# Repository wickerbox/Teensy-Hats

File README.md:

# Teensy-Hats
Collection of daughter boards for Paul Stoffregen's Teensy

- LiDAR Teensy Hat
- Temperature Monitor Hat

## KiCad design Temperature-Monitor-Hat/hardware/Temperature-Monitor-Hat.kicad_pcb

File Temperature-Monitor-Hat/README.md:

# Temperature Monitor LCD Teensy Hat

Simple monitor hat with an LCD screen that displays current temperature as sensed by K-type thermocouple through the MAX31855 junction-compensated sensor chip. The board also buzzes at certain preset temperatures. 

|Ref|Qty|Description|Manufacturer|Mfr PN|Vendor|Vendor PN|
|---|---|-----------|------------|------|------|---------|
|J1|1|TEENSY 3.2 32BIT 72MHZ|PJRC|TEENSY3.2|PJRC|TEENSY3.2|
|U1|1|IC CONV THERMOCOUPLE MAX31855 SOIC8|Freescale NXP|MAX31855KASA+|Digikey|MAX31855KASA+-ND|
|LCD1|1|LCD MODULE 16X2 CHARACTER 1602A|Tinsharp|TC1602A-09T|Adafruit|181|
|C1;C2|2|CAP CER 0.1UF 100V X7R 0603|Murata|GRM188R72A104KA35D|Digikey|490-3285-1-ND|
|J2|1|CONN TERM SCREW GREEN 2.54MM 2POS TH|OnShoreTech|OSTVN02A150|Digikey|ED10561-ND|
|R1|1|TRIMMER 10K OHM TH|Bourns|3362U-1-103LF|Digikey|3362U-103LF-ND|
|SPK1|1|BUZZER ONE NOTE 3V 4KHZ PIEZO SMT|CUI Inc|CMT-1603-SMT-TR|Digikey|102-1193-1-ND|

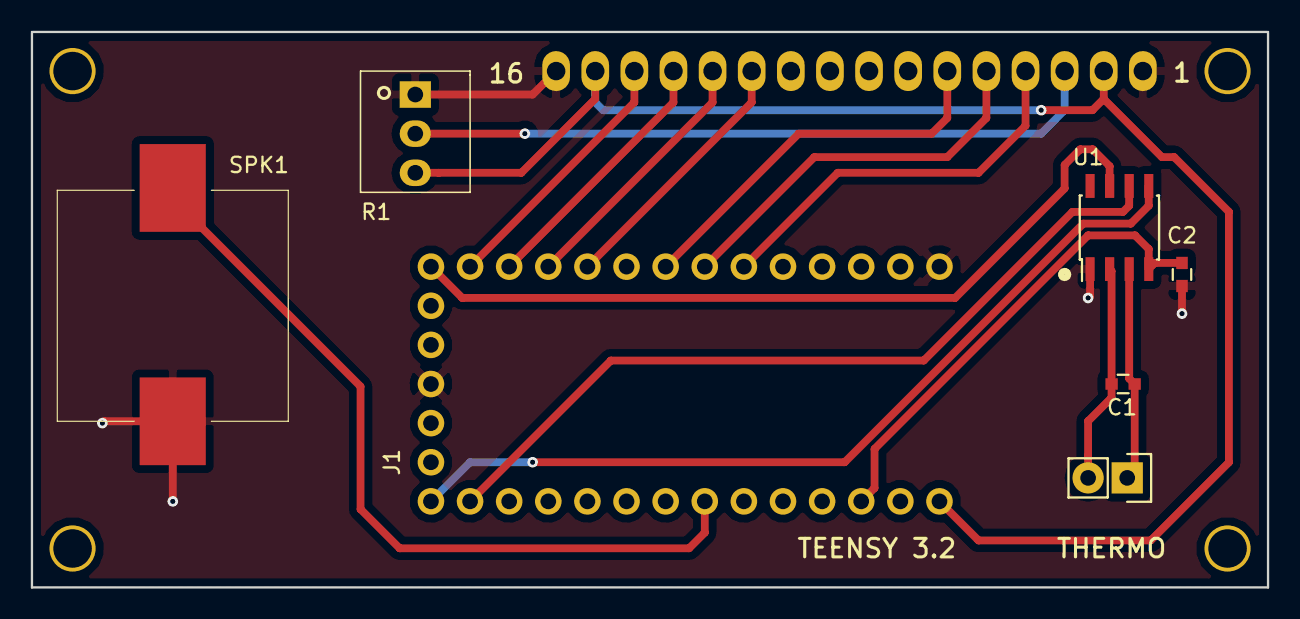
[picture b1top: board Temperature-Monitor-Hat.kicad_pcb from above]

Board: 2 copper layers, 80.3 x 36.1 mm, 8 parts (1 on the bottom side), 17 nets.

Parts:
C1, C2: 100nF; RLC-0603-SMD
J1: TEENSY3.2-72MHz; TEENSY-3.2-NOSILK
J2: THERMO; CONN-ONSHORE-SCREW-GREEN-2PIN-TH
LCD1: LCD-MODULE-16X2-CHARACTER-1602A-CUSTOM1; LCD-1602A
R1: 10K; RES-TRIMPOT-BOURNS-3362-SQUARE-TH-CENTER
SPK1: BUZZER; SPEAKER-CMT-1603
U1: MAX31855; SOIC-8-3.9x4.9MM-P1.27MM

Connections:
+3V3: C2.1, J1.3V1, J1.3V2, U1.4
+5V: J1.VIN, LCD1.2, LCD1.15, R1.3
GND: C2.2, J1.G1, J1.G2, LCD1.1, LCD1.16, R1.1, SPK1.2, U1.1
unnamed: C1.1, J2.1, U1.3
unnamed: C1.2, J2.2, U1.2
unnamed: J1.4, LCD1.4
unnamed: J1.5, LCD1.5
unnamed: J1.6, LCD1.6
unnamed: J1.8, LCD1.11
unnamed: J1.9, LCD1.12
unnamed: J1.10, LCD1.13
unnamed: J1.11, LCD1.14
unnamed: J1.12, U1.7
unnamed: J1.13, U1.5
unnamed: J1.14, U1.6
unnamed: J1.20, SPK1.1
unnamed: LCD1.3, R1.2

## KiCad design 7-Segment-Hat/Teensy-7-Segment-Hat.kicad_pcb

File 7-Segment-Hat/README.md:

# 7-Segment Display Teensy Hat

7-Segment display daughter board for the Teensy 3.2 with onboard microSD card.

I'll share the boards at OSH Park when the design is verified. You can buy a set of three for $5.20.

|Ref|Qty|Description|MF_Name|MF_PN|Digikey|
|---|---|-----------|-------|-----|-------|
|J3|1|CONN MICRO SD CARD HINGED TYPE|Molex|5009010801|WM19081CT-ND|
|LED1|1|LED DISPLAY 4CHAR 7SEGMENT COMMON CATHODE LTC-4727JR|LITE-ON|LTC-4727JR|160-1551-5-ND|
|R1-R4|4|RES SMD 470 OHM 5% 1/4W 0603|Rohm Semi|ESR03EZPJ471|RHM470DCT-ND|

The best way to place the LCD 7-Segment Display and the Teensy 3.2 is to buy one 40-position header (it's the cheapest option, about $0.50) and snap it apart into the sections you need.

The Teensy 3.2 can be bought from OSH Park at checkout, or from <a href="http://pjrc.com/store/teensy32.html">PJRC</a>.

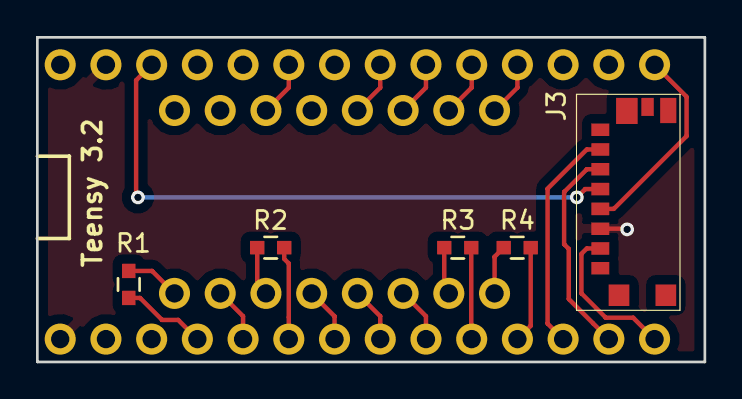
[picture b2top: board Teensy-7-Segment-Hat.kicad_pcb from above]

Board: 2 copper layers, 37.1 x 18.0 mm, 7 parts (1 on the bottom side), 23 nets.

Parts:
J1: TEENSY3.2-72MHz-SIMPLE; TEENSY-3.2-SIMPLE
J3: MICRO-SD; CONN-SD-MICRO-MOLEX-0475710001
LED1: LED-4x7-SEGMENT-LTC-4727JR; DIP-16-W10.16MM-CIRCLEPADS
R1, R2, R3, R4: 470; RLC-0603-SMD

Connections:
+3V3: J1.3V2, J3.4
/A: J1.18, LED1.14
/B: J1.16, LED1.16
/C: J1.19, LED1.13
/D: J1.7, LED1.3
/DIGIT1: J1.9, R4.1
/DIGIT2: J1.8, R3.1
/DIGIT3: J1.4, R2.1
/DIGIT4: J1.2, R1.1
/DP: J1.3, LED1.7
/E: J1.5, LED1.5
/F: J1.21, LED1.11
/G: J1.17, LED1.15
/L: J1.6, LED1.4
/MISO: J1.12, J3.7
/MOSI: J1.11, J3.3
/SCLK: J1.13, J3.5
/SD_CS: J1.10, J3.2
GND: J1.AG, J1.G1, J3.6
unnamed: LED1.1, R4.2
unnamed: LED1.2, R3.2
unnamed: LED1.6, R2.2
unnamed: LED1.8, R1.2

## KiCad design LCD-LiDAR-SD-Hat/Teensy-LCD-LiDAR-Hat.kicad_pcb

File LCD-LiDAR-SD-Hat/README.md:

# LCD-LiDAR-SD Teensy Hat

LiDAR board with LCD screen and SD card for logging. 

The project is released as open hardware under the CERN v1.2 Open Hardware license.

It uses a LiDAR-Lite v1 or v2 for the rangefinder, and it supports the I2C and PWM modes. The project uses the KiCad Teensy template and footprint from <a href="http://wickerbox.net/wickerlib">wickerlib</a>. 

I've shared the project at OSH Park so you can buy a set of three bare boards for $22.55.

The Teensy 3.2 is available at <a href="http://pjrc.com/teensy/index.html">PJRC.com</a> or at OSH Park as an add-on at checkout.

I'm using a standard <a href="https://www.adafruit.com/product/181">16x2 LCD screen from Adafruit</a>, but you can also get them from Amazon.

The rest of the parts are available at <a href="http://digikey.com">Digikey</a>.

|Ref|Qty|Description|Manuf|Mfr PN|Source PN|
|---|---|-----------|-----|------|---------|
|J2|1|HEADER FEMALE 6POS TH 1x06 0.1”|Harwin|M20-7820642|952-1808-ND|
|J3|1|CONN MICRO SD CARD |Molex|0475710001|WM9731CT-ND|
|LED1-2|2|LED AMBER DIFFUSED 0603 SMD|OSRAM Opto|LA L296-Q2R2-1-Z|475-2712-1-ND|
|R1-R5,R7|6|RES SMD 1K OHM 1% 1/10W 0603|Samsung|RC1608F102CS|1276-3484-1-ND|
|R6|1|TRIMMER 10K OHM TH |Bourns| 3362U-1-103LF|3362U-103LF-ND|
|S1-S3|3|SWITCH TACTILE SPST-NO 0.05A 12V|Omron|B3U-1000P|SW1020CT-ND|

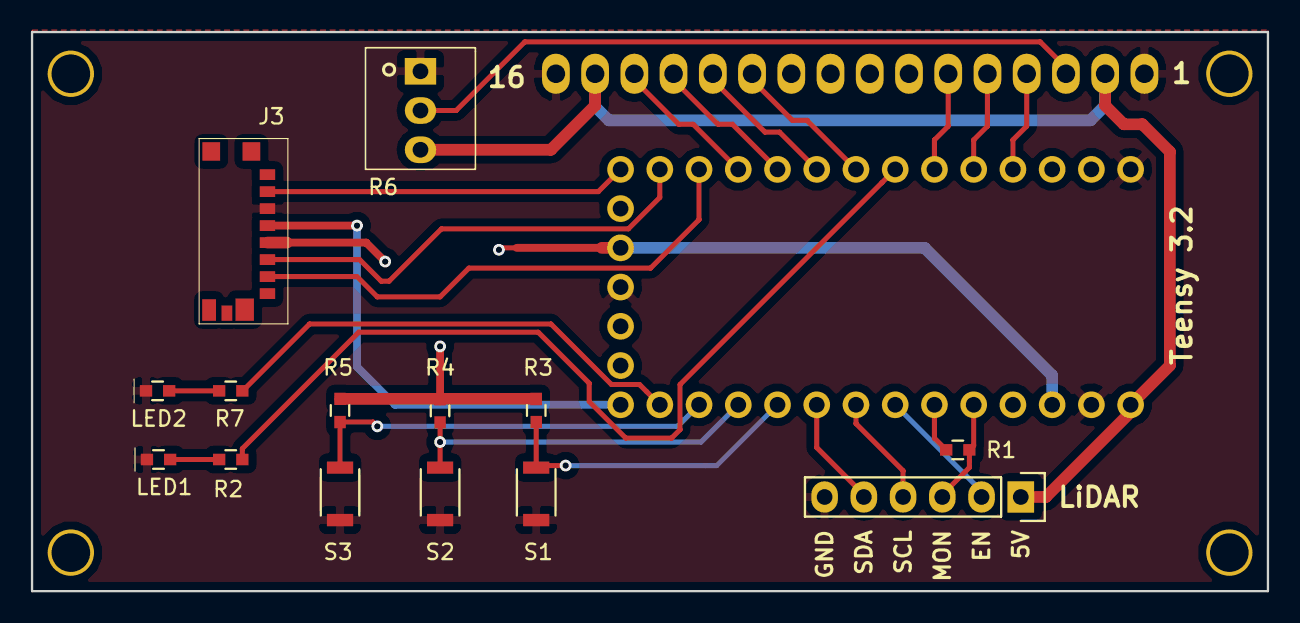
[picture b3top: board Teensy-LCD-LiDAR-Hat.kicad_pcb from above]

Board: 2 copper layers, 80.0 x 36.2 mm, 16 parts (1 on the bottom side), 27 nets.

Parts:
J1: TEENSY3.2-72MHz; TEENSY-3.2-NOSILK
J2: LIDAR-LITE; CONN-HEADER-STRAIGHT-P2.54MM-1x06
J3: MICRO-SD; CONN-SD-MICRO-MOLEX-0475710001
LCD1: LCD-16x2; LCD-1602A
LED1, LED2: AMBER; LED-0603-SMD
R1, R2, R3, R4, R5, R7: 1K; RLC-0603-SMD
R6: 10K; RES-TRIMPOT-BOURNS-3362-SQUARE-TH-CENTER
S1: BUTTON1; SWITCH-OMRON-MOMENTARY-SMD-B3U-1000P
S2: BUTTON2; SWITCH-OMRON-MOMENTARY-SMD-B3U-1000P
S3: BUTTON3; SWITCH-OMRON-MOMENTARY-SMD-B3U-1000P

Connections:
+3V3: J1.3V1, J1.3V2, J3.4, R3.1, R4.1, R5.1
+5V: J1.VIN, J2.1, LCD1.2, LCD1.15, R6.3
/BUTTON1: J1.17, R3.2, S1.1
/BUTTON2: J1.16, R4.2, S2.1
/BUTTON3: J1.15, R5.2, S3.1
/LCD_D4: J1.6, LCD1.11
/LCD_D5: J1.7, LCD1.12
/LCD_D6: J1.8, LCD1.13
/LCD_D7: J1.9, LCD1.14
/LCD_EN: J1.4, LCD1.6
/LCD_RS: J1.2, LCD1.4
/LCD_RW: J1.3, LCD1.5
/LED1: J1.5, R2.1
/LED2: J1.14, R7.1
/LIDAR_EN: J1.20, J2.2
/LIDAR_MONITOR: J1.22, J2.3, R1.2
/LIDAR_TRIGGER: J1.21, R1.1
/MISO: J1.12, J3.7
/MOSI: J1.11, J3.3
/SCL: J1.19, J2.4
/SCLK: J1.13, J3.5
/SDA: J1.18, J2.5
/SD_CS: J1.10, J3.2
GND: J1.AG, J1.G1, J1.G2, J2.6, J3.6, LCD1.1, LCD1.16, LED1.1, LED2.1, R6.1, S1.2, S2.2, S3.2
unnamed: LCD1.3, R6.2
unnamed: LED1.2, R2.2
unnamed: LED2.2, R7.2

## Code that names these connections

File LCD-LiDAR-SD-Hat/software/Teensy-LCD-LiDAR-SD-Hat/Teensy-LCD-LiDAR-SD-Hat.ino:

/***************************************************

  Jenner Hanni / Wickerbox Electronics Notes
  See the Github repo: https://github.com/wickerbox/Teensy-Hats/

****************************************************/


#include <SPI.h>
#include "SdFat.h"
#include <LiquidCrystal.h>

// Hook up to the SD card over SPI
// Assumes 11 MOSI, 12 MISO, 13 SCLK
int SDCS_Pin = 10;
SdFat SD;

// LCD
// LiquidCrystal lcd(rs, rw, enable, d4, d5, d6, d7)
LiquidCrystal lcd(2, 3, 4, 6, 7, 8, 9);

// LEDs and Buttons
int LED1_Pin = 5;
int LED2_Pin = 14;
int Button1_Pin = 17;
int Button2_Pin = 16;
int Button3_Pin = 15;

// LiDAR Setup
int LiDAR_Trigger_Pin = 21;
int LiDAR_Monitor_Pin = 22;
int LiDAR_Enable_Pin = 20;
int LiDAR_SDA_Pin = 18;
int LiDAR_SCL_Pin = 19;
unsigned long pulse_width;

void readLiDAR() {
  pulse_width = pulseIn(LiDAR_Monitor_Pin, HIGH); // Count how long the pulse is high in microseconds
  if (pulse_width != 0) { // If we get a reading that isn't zero, let's print it
    pulse_width = pulse_width / 10; // 10usec = 1 cm of distance for LIDAR-Lite
  }
}

void setup() {

  Serial.begin(9600);
  delay(1000);
  Serial.println("The program is on.");
  delay(1000);

  // Setup the LiDAR Rangefinder
  pinMode(LiDAR_Trigger_Pin, OUTPUT);
  pinMode(LiDAR_Monitor_Pin, INPUT);
  pinMode(LiDAR_Enable_Pin, OUTPUT);
  digitalWrite(LiDAR_Enable_Pin, HIGH); // turn sensor on
  digitalWrite(LiDAR_Trigger_Pin, LOW); // set for continuous read

  // Setup the buttons and LEDs
  pinMode(LED1_Pin, OUTPUT);
  pinMode(LED2_Pin, OUTPUT);
  pinMode(Button1_Pin, INPUT);
  pinMode(Button2_Pin, INPUT);
  pinMode(Button2_Pin, INPUT);

  // LED Test
  digitalWrite(LED1_Pin, HIGH);
  digitalWrite(LED2_Pin, HIGH);
  delay(2000);
  digitalWrite(LED1_Pin, LOW);
  digitalWrite(LED2_Pin, LOW);

  // Setup the LCD
  lcd.begin(16, 2);
  lcd.print("LCD-LiDAR-SD Hat");
  
}

void loop() {
  // check buttons
  digitalWrite(LED1_Pin, not(digitalRead(Button1_Pin)));
  digitalWrite(LED2_Pin, not(digitalRead(Button2_Pin)));
  
  // check lidar
  readLiDAR();
  
  // update LCD
  lcd.setCursor(0, 1);
  lcd.print("Range: ");
  lcd.print(pulse_width);
}

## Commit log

2016-07-31 Created v1.0 design, created stencils and gerbers. Ready to order.
2016-07-31 Added README
2016-07-31 Added preview image.
2016-08-13 Ordered boards, parts, and stencil.
2016-08-13 Added BOM, updated README.
2016-08-13 Table fix.
2016-08-14 Created board. Ready to order.
2016-08-17 Ordered boards and parts.
2016-08-24 Added board outline to assembly diagrams.
2016-08-27 Assembled and tested.
2016-08-30 Adjusted code location. Added photos.
2016-08-31 Updated README. Added code for LiDar hat.
2016-08-31 Rotated image 180 degrees.
2016-08-31 Image won't rotate on github.

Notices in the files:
Temperature-Monitor-Hat/hardware/Temperature-Monitor-Hat.kicad_pcb:
Released under the CERN Open Hardware License v1.2
